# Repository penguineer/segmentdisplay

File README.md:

segmentdisplay
==============

Playing around with segment displays

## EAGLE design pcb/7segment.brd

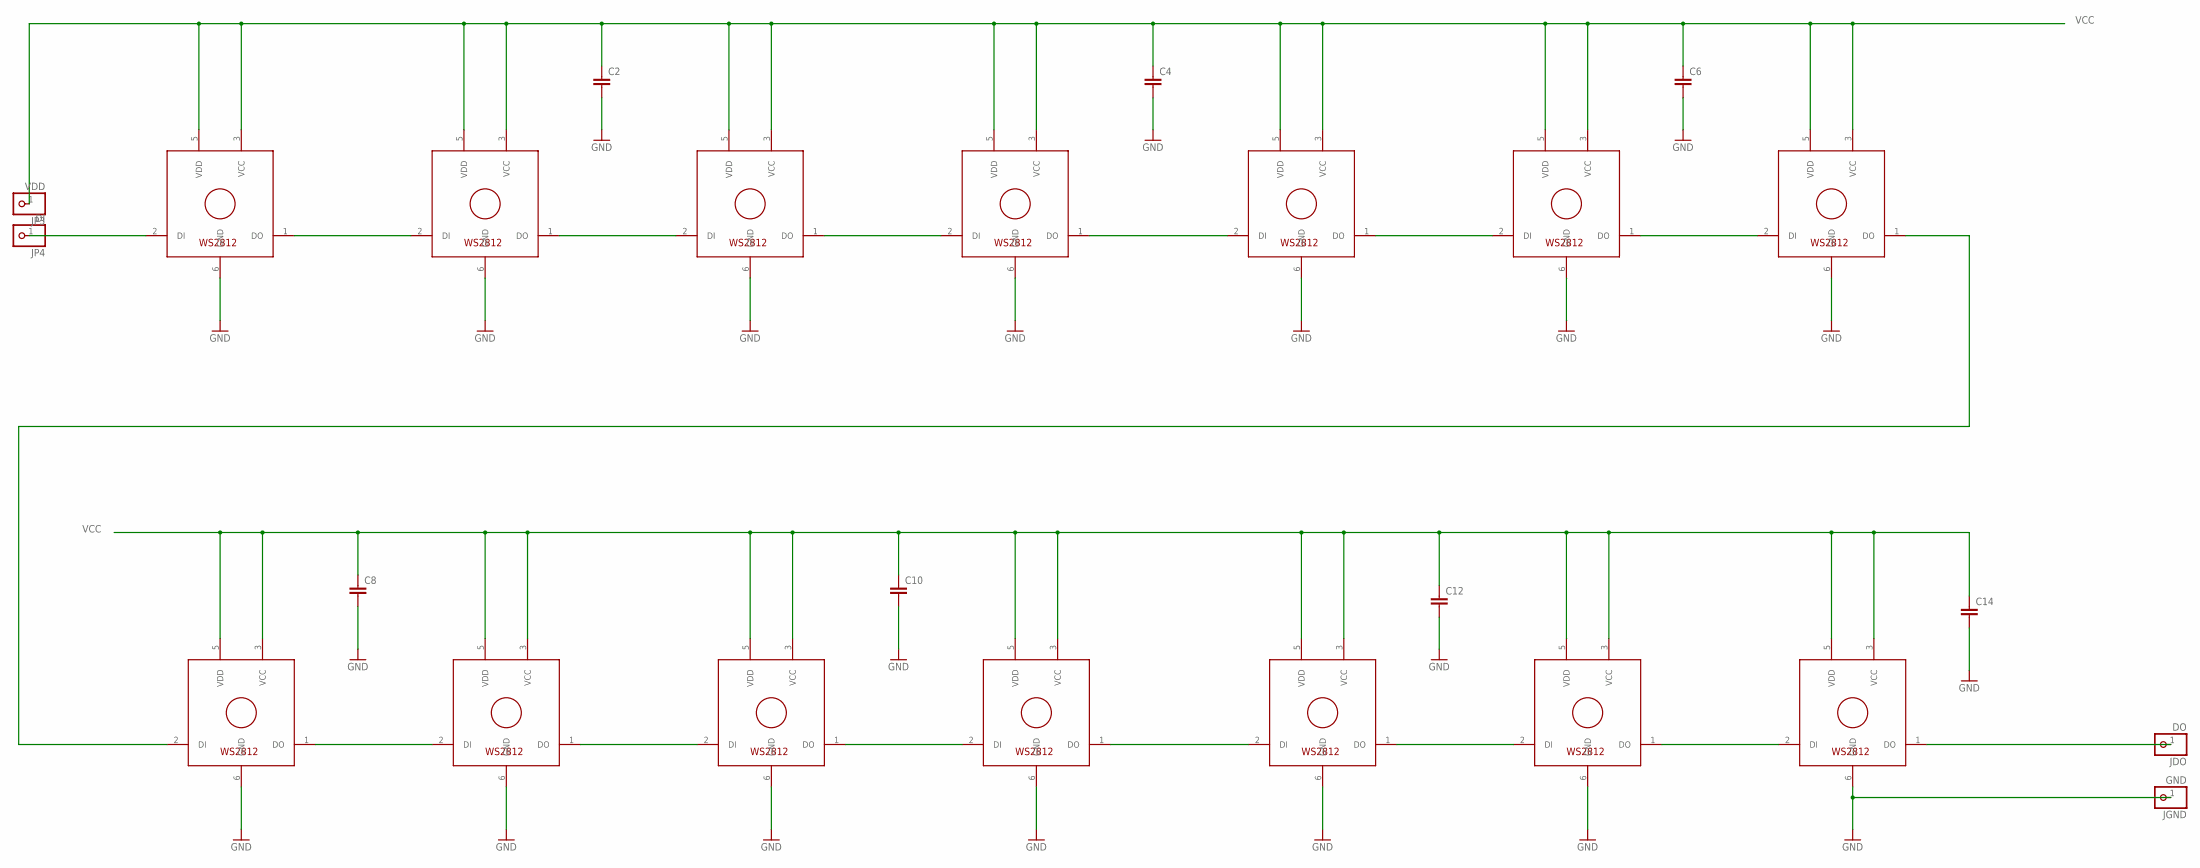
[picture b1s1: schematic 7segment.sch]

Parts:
C2, C4, C6, C8, C10, C12, C14: C-EUC1206; C1206
JDO: DO; 1X01
JGND: GND; 1X01
JP3: VDD; 1X01
JP4: DI; 1X01
U1, U2, U3, U4, U5, U6, U7, U8, U9, U10, U11, U12, U13, U14: WS2812

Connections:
GND: C2.2, C4.2, C6.2, C8.2, C10.2, C12.2, C14.2, JGND.1, U1.6 (GND), U2.6 (GND), U3.6 (GND), U4.6 (GND), U5.6 (GND), U6.6 (GND), U7.6 (GND), U8.6 (GND), U9.6 (GND), U10.6 (GND), U11.6 (GND), U12.6 (GND), U13.6 (GND), U14.6 (GND)
JDI: JP4.1, U1.2 (DI)
unnamed: U1.1 (DO), U2.2 (DI)
unnamed: U2.1 (DO), U3.2 (DI)
unnamed: U7.1 (DO), U8.2 (DI)
unnamed: JDO.1, U14.1 (DO)
unnamed: U3.1 (DO), U4.2 (DI)
unnamed: U4.1 (DO), U5.2 (DI)
unnamed: U5.1 (DO), U6.2 (DI)
unnamed: U6.1 (DO), U7.2 (DI)
unnamed: U8.1 (DO), U9.2 (DI)
unnamed: U9.1 (DO), U10.2 (DI)
unnamed: U10.1 (DO), U11.2 (DI)
unnamed: U11.1 (DO), U12.2 (DI)
unnamed: U12.1 (DO), U13.2 (DI)
unnamed: U13.1 (DO), U14.2 (DI)
VCC: C2.1, C4.1, C6.1, C8.1, C10.1, C12.1, C14.1, JP3.1, U1.3 (VCC), U1.5 (VDD), U2.3 (VCC), U2.5 (VDD), U3.3 (VCC), U3.5 (VDD), U4.3 (VCC), U4.5 (VDD), U5.3 (VCC), U5.5 (VDD), U6.3 (VCC), U6.5 (VDD), U7.3 (VCC), U7.5 (VDD), U8.3 (VCC), U8.5 (VDD), U9.3 (VCC), U9.5 (VDD), U10.3 (VCC), U10.5 (VDD), U11.3 (VCC), U11.5 (VDD), U12.3 (VCC), U12.5 (VDD), U13.3 (VCC), U13.5 (VDD), U14.3 (VCC), U14.5 (VDD)

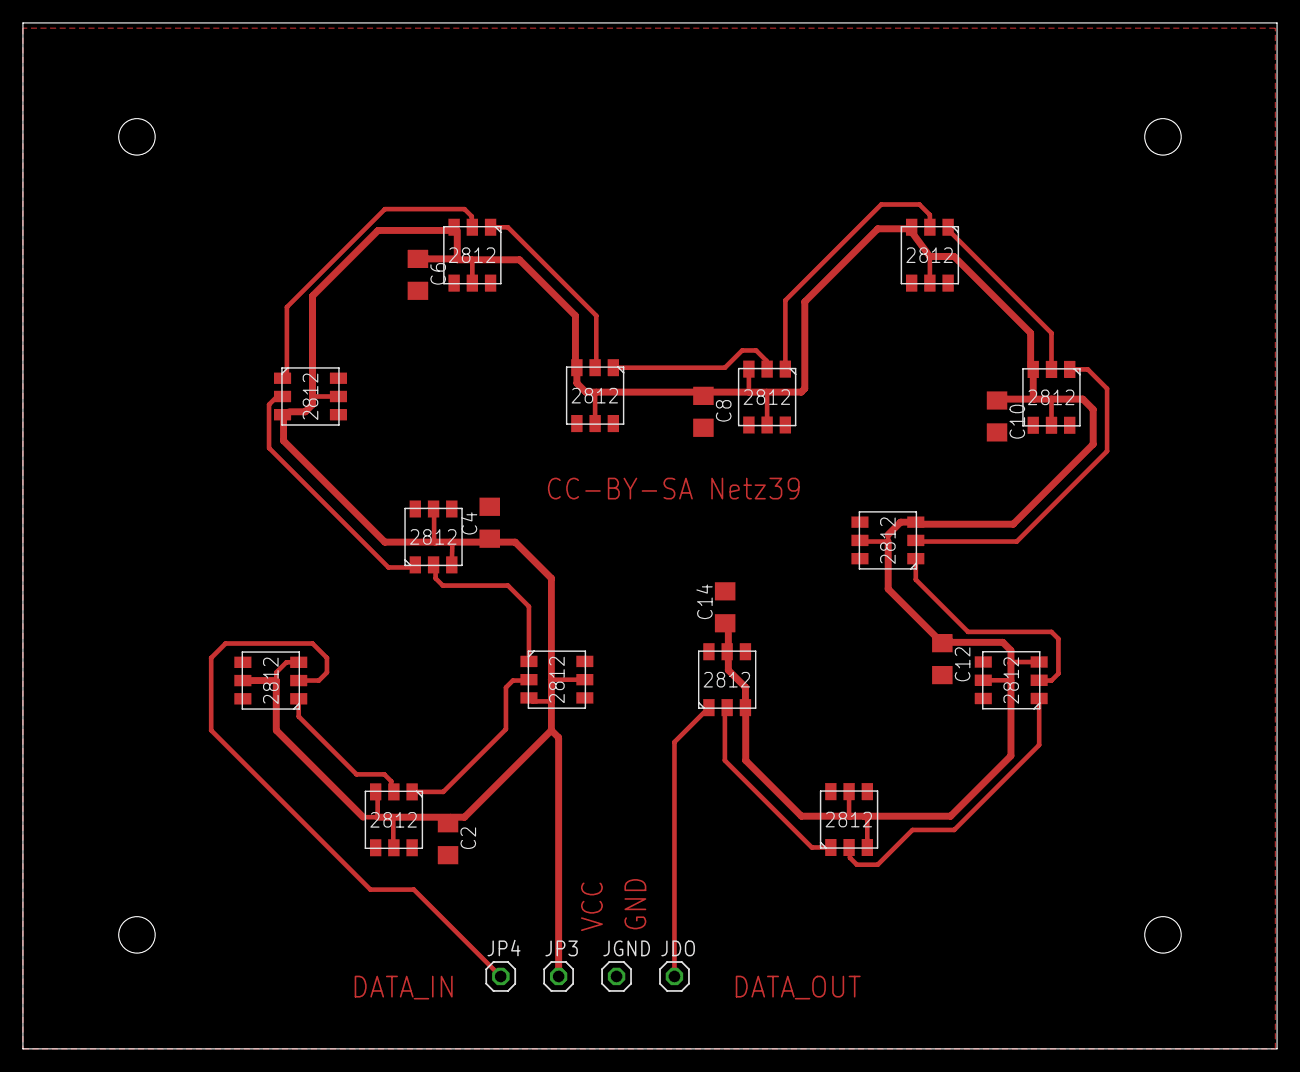
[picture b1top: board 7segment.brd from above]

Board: 2 copper layers, 110.0 x 90.0 mm, 25 parts (0 on the bottom side), 17 nets.

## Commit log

2014-06-25 7 segment display: frame and inlays
2014-06-28 Production files
2014-06-28 dimensions for 7 segment pcb
2014-06-28 converter for dxf 2 dimension
2014-06-28 Schema and Board for WS2812 segment lights
2014-06-28 Basic Firmware
2014-06-28 BCD coding and test program
2014-06-28 PCB subdir
2014-08-04 FreeCad-File for 7segment single number
2014-08-04 gitignore for firmware build
2015-04-28 FPGA: directory and gitignore file
    Be sure to include all necessary files – it is pointless to start excluding.
2015-05-01 FPGA: Initial commit
    Symbol Generator, Pixel Generator and Digit Sequencer

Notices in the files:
pcb/7segment.brd:
CC-BY-SA Netz39
